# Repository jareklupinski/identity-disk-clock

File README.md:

# identity-disk-clock
An LED wall clock inspired by Tron

Watching the movie Tron Legacy, I wondered if I could turn their identity disk design into an LED clock. Work in progress!

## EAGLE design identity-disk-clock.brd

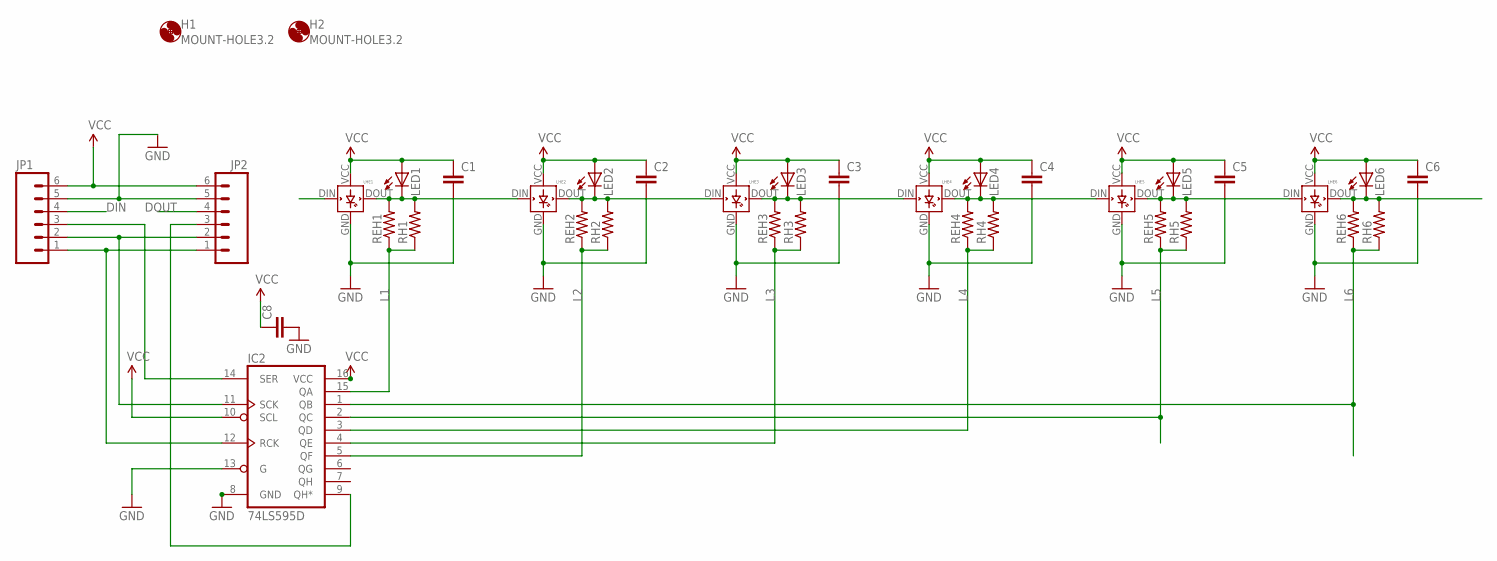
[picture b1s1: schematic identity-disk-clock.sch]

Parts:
C1, C2, C3, C4, C5, C6: C-EU050-024X044; C050-024X044
C8: C-EUC0402; C0402
H1, H2: MOUNT-HOLE3.2; 3,2
IC2: 74LS595D; SO16
JP1, JP2: M06LOCK; 1X06_LOCK
LED1, LED2, LED3, LED4, LED5, LED6: LEDMICRO-SIDELED; MICRO-SIDELED
LHE1, LHE2, LHE3, LHE4, LHE5, LHE6: WS2812B; LED5MMRGBNP
REH1, REH2, REH3, REH4, REH5, REH6: R-US_R0402; R0402
RH1, RH2, RH3, RH4, RH5, RH6: R-US_0204/5; 0204/5

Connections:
DIN: JP1.4, LHE1.DIN
DOUT: JP2.4, LED6.C, LHE6.DOUT, REH6.2, RH6.2
GND: C1.2, C2.2, C3.2, C4.2, C5.2, C6.2, C8.2, IC2.8 (GND), IC2.13 (G), JP1.5, JP2.5, LHE1.GND, LHE2.GND, LHE3.GND, LHE4.GND, LHE5.GND, LHE6.GND
L1: IC2.15 (QA), REH1.1, RH1.1
L2: IC2.5 (QF), REH2.1, RH2.1
L3: IC2.4 (QE), REH3.1, RH3.1
L4: IC2.3 (QD), REH4.1, RH4.1
L5: IC2.2 (QC), REH5.1, RH5.1
L6: IC2.1 (QB), REH6.1, RH6.1
unnamed: LED1.C, LHE1.DOUT, LHE2.DIN, REH1.2, RH1.2
unnamed: LED2.C, LHE2.DOUT, LHE3.DIN, REH2.2, RH2.2
unnamed: LED3.C, LHE3.DOUT, LHE4.DIN, REH3.2, RH3.2
unnamed: LED4.C, LHE4.DOUT, LHE5.DIN, REH4.2, RH4.2
unnamed: LED5.C, LHE5.DOUT, LHE6.DIN, REH5.2, RH5.2
unnamed: IC2.11 (SCK), JP1.2, JP2.2
unnamed: IC2.12 (RCK), JP1.1, JP2.1
unnamed: IC2.14 (SER), JP1.3
unnamed: IC2.9 (QH*), JP2.3
VCC: C1.1, C2.1, C3.1, C4.1, C5.1, C6.1, C8.1, IC2.10 (SCL), IC2.16 (VCC), JP1.6, JP2.6, LED1.A, LED2.A, LED3.A, LED4.A, LED5.A, LED6.A, LHE1.VCC (VDD), LHE2.VCC (VDD), LHE3.VCC (VDD), LHE4.VCC (VDD), LHE5.VCC (VDD), LHE6.VCC (VDD)

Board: 2 copper layers, 36 parts (0 on the bottom side), 19 nets, no tracks yet.

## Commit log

2018-07-06 work in progress

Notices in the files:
parts and their libraries:
SparkFun-DigitalIC: Licensing: CC v3.0 Share-Alike You are welcome to use this library for commercial purposes.
